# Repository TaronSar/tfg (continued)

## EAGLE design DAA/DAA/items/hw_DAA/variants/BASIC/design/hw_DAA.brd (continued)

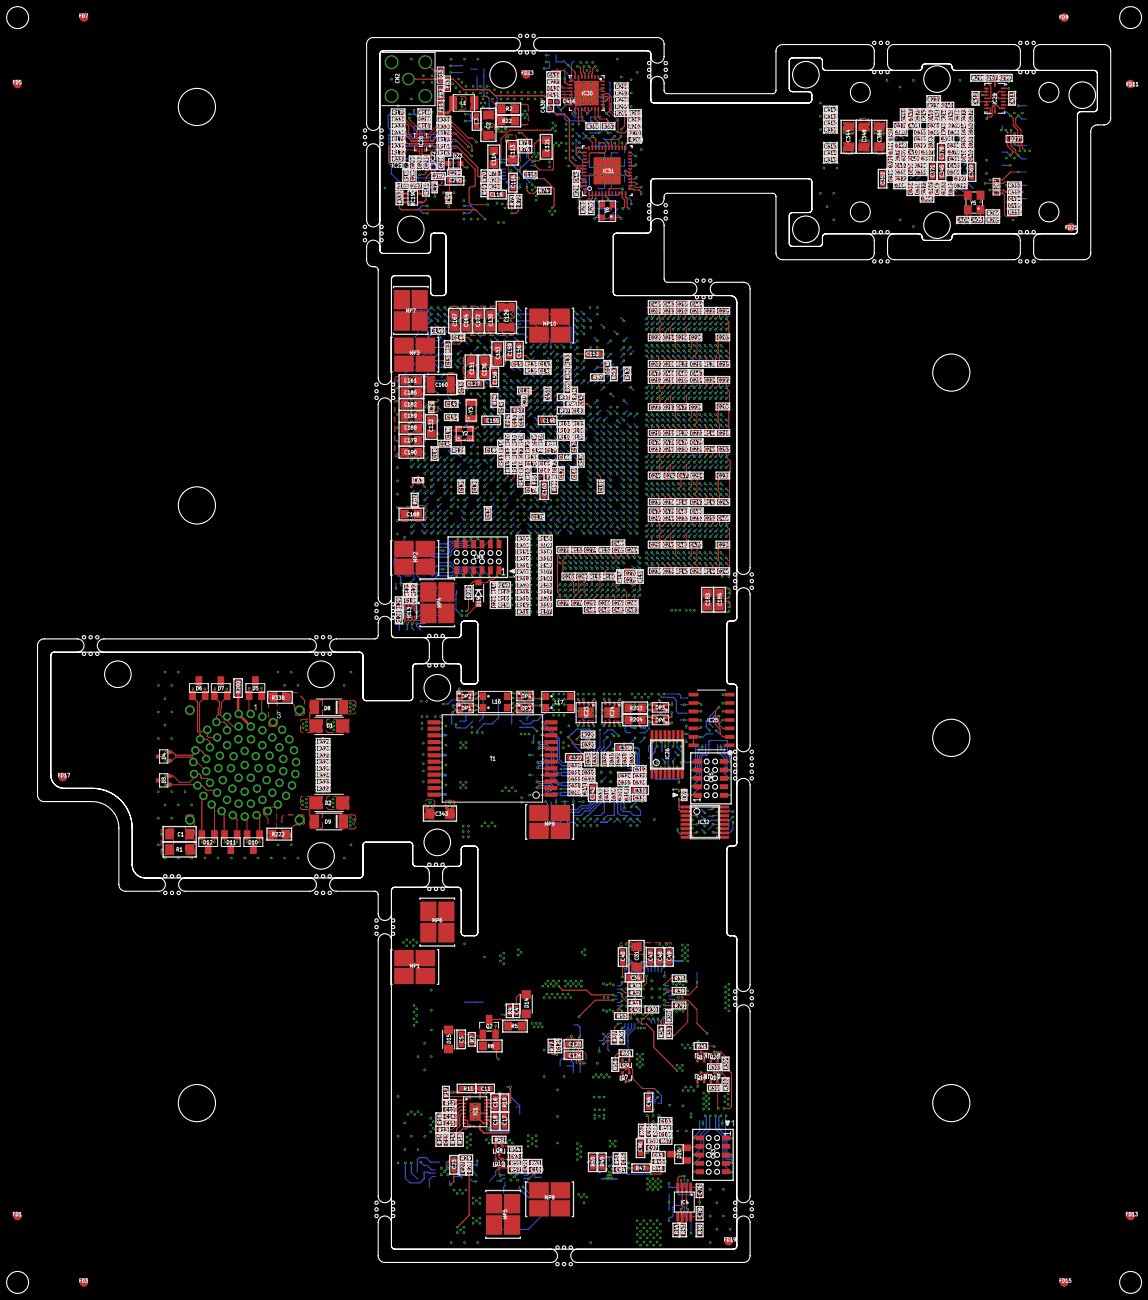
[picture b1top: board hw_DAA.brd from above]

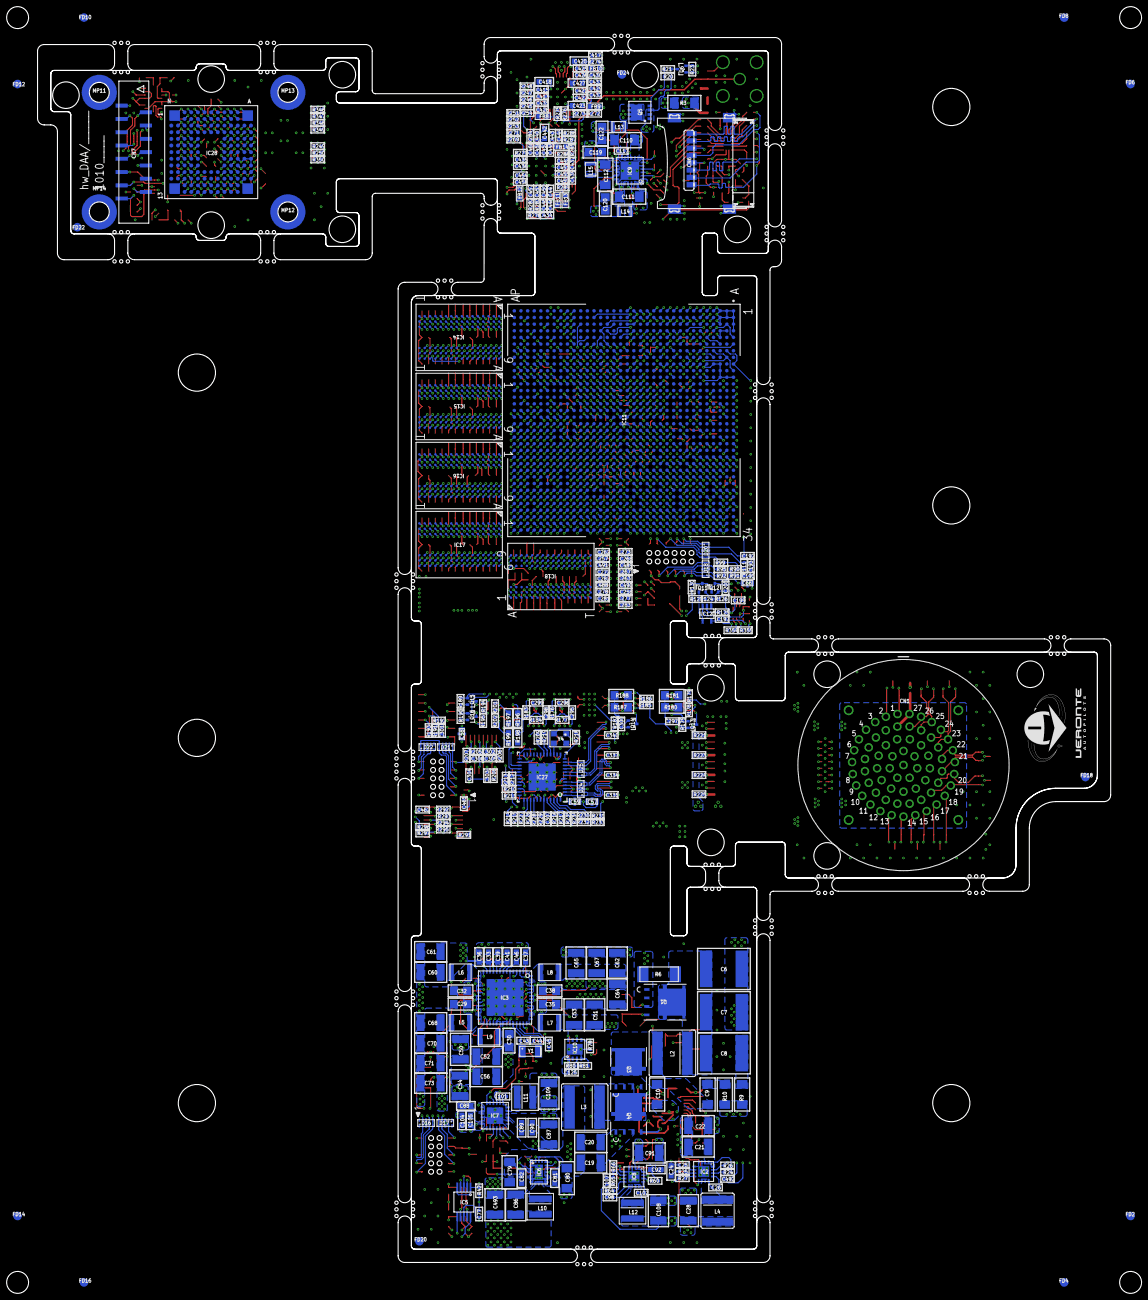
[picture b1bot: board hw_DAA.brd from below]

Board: 16 copper layers, 161.6 x 184.5 mm, 1022 parts (366 on the bottom side), 632 nets.

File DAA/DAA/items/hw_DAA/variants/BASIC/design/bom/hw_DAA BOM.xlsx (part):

Version | 101010
Schematics Name | hw_DAA.sch
Designer Name | Embention Sistemas Inteligentes S.A.
Date | 45559.0
QUANTITY | VALUE | DEVICE | PARTS | P/Ns
121 | 100nF,10%,0402,50V | C_0402 | C101, C102, C117, C137, C173, C192, C193, C196, C197, C199, C221, C224, C225, C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 | GCM155R71H104KE02D | GCM155L8EH104KE07D
7 | 100nF,10%,0603,100V | C_0603 | C11, C16, C3, C81, C82, C90, C92 | HMJ107BB7104KAHT | MCJCH168BB7104KTPA01
1 | 100pF,5%,0402,50V | C_0402 | C198 | GCM1555C1H101JA16D
18 | 100uF,20%,0805,4V | C_0805 | C130, C131, C132, C133, C136, C161, C164, C167, C168, C172, C179, C182, C183, C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 | GRM21BC80G107ME15L | GRM21BC80G107ME15K | CL21X107MRYN3WE
3 | 100uF,20%,1210,6.3V | C_1210 | C108, C109, C86 | GRT32ER60J107ME13L
19 | 10nF,10%,0402,50V | C_0402 | C284, C307, C325, C328, C335, C341, C413, C421, C425, C428, C429, C430, C447, C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 | CGA2B3X8R1H103K050BB
1 | 10pF,1%,0402,50V | C_0402 | C85 | GCQ1555C1H100FB01D
11 | 10uF,10%,0805,16V | C_0805 | C113, C114, C119, C120, C121, C122, C29, C30, C32, C35, C38 | EMK212BBJ106KGHT | CGA4J1X5R1C106K125AC
4 | 10uF,10%,1206,35V | C_1206 | C110, C111, C112, C2 | CGA5L1X7R1V106K160AC | CGA5L1X7R1H106K160AC
3 | 10uF,10%,2220,100V | C_2220K | C6, C7, C8 | CGA9N3X7S2A106K230KB
25 | 10uF,20%,0402,4V | C_0402 | C128, C141, C142, C143, C145, C146, C147, C148, C151, C153, C154, C157, C162, C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 | GRT155D70G106ME13J | GRT155D70G106ME13D | KAM05CT70G106KH
19 | 10uF,20%,0603,10V | C_0603 | C104, C105, C293, C327, C332, C338, C342, C345, C352, C369, C371, C378, C418, C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 | GRT188C81A106ME13D
10 | 10uF,20%,0603,4V,3L | NFM18HC106D0G3L | C55, C57, C58, C59, C63, C66, C69, C72, C74, C75 | NFM18HC106D0G3L
1 | 120pF,5%,0402,50V | C_0402 | C25 | GCM1555C1H121JA16D
2 | 12pF,5%,0402,50V | C_0402 | C43, C44 | GCM1555C1H120JA16J
2 | 15nF,10%,0402,50V | C_0402 | C419, C441 | GCM155R71H153KA55D
2 | 1nF,10%,1206,2KV | C_1206 | C1, C343 | C1206C102KGRACAUTO
64 | 1uF,10%,0402,25V | C_0402 | C115, C209, C212, C215, C218, C219, C220, C222, C223, C237, C240, C243, C246, C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 | GRT155R61E105KE01D
2 | 1uF,10%,0603,16V | C_0603 | C34, C94 | C0603C105K4RACAUTO
12 | 2.2uF,10%,0402,16V | C_0402 | C213, C214, C216, C217, C241, C242, C244, C245, C269, C270, C417, C440 | GRT155C81C225KE13D
16 | 2.2uF,10%,0603,16V | C_0603 | C116, C118, C123, C126, C18, C33, C36, C37, C39, C40, C41, C46, C47, C48, C49, 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 | CGA3E1X7S1C225K080AC
3 | 2.7nF,5%,0603,50V | C_0603 | C23, C24, C96 | C0603X272J5GAC7867
2 | 220nF,10%,0402,35V | C_0402 | C103, C408 | CGA2B1X7R1V224K050BC
1 | 22nF,10%,0402,50V | C_0402 | C414 | C0402C223K5RECAUTO
4 | 22pF,0.25pF,0402,50V | C_0402 | C100, C194, C195, C97 | 04025A220C4T2A
4 | 22uF,10%,1206,16V | C_1206 | C31, C344, C348, C386 | GRT31CC81C226KE01L
2 | 3.3nF,10%,0402,50V | C_0402 | C95, C98 | GCM155R71H332KA37J
1 | 330pF,10%,0402,50V | C_0402 | C106 | GRT155R71H331KE01D
2 | 330uF,20%,1210,2.5V | C_1210 | C129, C160 | GRM32EC80E337ME05L
1 | 33nF,10%,0402,50V | C_0402 | C438 | CGA2B3X7R1H333K050BB | GCM155R71H333KE02D
1 | 33pF,5%,0402,50V | C_0402 | C191 | GCM1555C1H330JA16D
1 | 390pF,10%,0402,50V | C_0402 | C13 | GCM155R71H391KA37D
3 | 4.7nF,20%,0402,100V | C_0402 | C297, C300, C84 | GCM155R72A472MA37D | GCM155R72A472KA37D | CL05B472KC5VPNC
50 | 4.7uF,20%,0402,10V | C_0402 | C135, C138, C139, C144, C149, C150, C201, C202, C203, C204, C205, C206, C207, C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 | GRT155R61A475ME13D
4 | 4.7uF,20%,1206,100V | C_1206 | C10, C79, C80, C9 | GRM31CC72A475ME11L
13 | 470nF,10%,0402,16V | C_0402 | C134, C171, C255, C42, C463, C466, C469, C474, C476, C479, C481, C483, C485 | CGA2B1X7S1C474K050BC
21 | 47uF,10%,1210,10V | C_1210 | C21, C22, C28, C50, C51, C52, C53, C54, C56, C60, C61, C62, C64, C65, C67, C68,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 | GCM32EC71A476KE02K
8 | 47uF,20%,0603,4V | C_0603 | C127, C140, C152, C155, C156, C158, C159, C163 | AMK107BC6476MA-RE | MSASA168BC6476MRCA01
1 | 56nF,10%,0402,16V | C_0402 | C12 | GCM155R71C563KA55J
1 | 6.8pF,5%,0603,100V | C_0603 | C17 | 06031A6R8J4T4A | CGA3E2NP02A6R8D080AA
2 | 6.8uF,20%,1210,50V | C_1210 | C19, C20 | CGA6P3X7S1H685M250AB
10 | 68nF,10%,0402,50V | C_0402 | C256, C464, C467, C471, C475, C477, C480, C482, C484, C486 | CGA2B3X7R1H683K050BB
2 | 8.2nF,10%,0402,16V | C_0402 | C14, C99 | C0402C822K4RACAUTO
2 | 820pF,10%,0402,50V | C_0402 | C15, C405 | GCG155R71H821KA01D
1 | 132203-18 | 132203-18 | CN2 | 132203-18
1 | 47219-2001 | SD-LATCH | CN6 | 47219-2001
2 | CLP-105-02-F-D-BE | CLP-105-02-F-D-BE | CN3, CN5 | CLP-105-02-F-D-BE
1 | CLP-106-02-F-D-BE | CLP-106-02-F-D-BE | CN4 | CLP-106-02-F-D-BE
1 | AQ4020-01FTG | AQ4020-01FTG | D23 | AQ4020-01FTG
2 | BZD27C10P-HE3-08 | BZD27C10P-HE3-08 | D14, D15 | BZD27C10P-HE3-08
1 | BZT52C3V3-7-F | BZT52C3V3-7-F | D19 | BZT52C3V3-7-F
4 | GSOT05C-HE3-08 | GSOT05C-HE3-08 | D10, D11, D12, D26 | GSOT05C-HE3-08
3 | HSP051-4M10 | HSP051-4M10CN | D24, D25, D27 | HSP051-4M10
1 | PESD15VL2BT-QR | SP712-02HTG | D5 | PESD15VL2BT-QR
2 | PESD2CANFD27V-UX | PESD2CANFD27V-UX | D3, D4 | PESD2CANFD27V-UX
7 | RCLAMP3324PQTCT | RCLAMP3324PQTCT | D16, D17, D18, D20, D21, D22, D28 | RCLAMP3324PQTCT
2 | SMA6J64CA | SZ1SMA36CAT3G | D1, D2 | SMA6J64CA
2 | SP712-02HTG | SP712-02HTG | D6, D7 | SP712-02HTG
2 | STPS5H100AFY | PMEG10030ELPX | D8, D9 | STPS5H100AFY
4 | BLM15PX121SH1D | BLM15PX121SH1D | FB4, FB5, FB6, FB7 | BLM15PX121SH1D
7 | BLM18AG102BH1D | BLM18HE152SZ1D | FB10, FB11, FB12, FB13, FB14, FB8, FB9 | BLM18AG102BH1D
3 | BLM18HE152SZ1D | BLM18HE152SZ1D | FB1, FB2, FB3 | BLM18HE152SZ1D
1 | BMI088 | BMI088 | IC29 | BMI088
1 | DP83867ERGZT | DP83867ERGZ | IC27 | DP83867ERGZT
1 | DS90UB954TRGZTQ1 | DS90UB954-Q1 | IC31 | DS90UB954TRGZTQ1
2 | ECS-2520MVQ-250-CN-TR | ECS-2520MVQ-250-CN-TR | Y4, Y6 | ECS-2520MVQ-250-CN-TR
1 | IMX296LQR-C | IMX296NSMD | IC28 | IMX296LQR-C
1 | LM5146QRGYRQ1 | LM5146-Q1 | IC1 | LM5146QRGYRQ1
5 | MT40A1G16TD-062E AAT_F | MT40A1G16TD-062ENSMD | IC14, IC15, IC16, IC17, IC18 | MT40A1G16TD-062E AAT:F
1 | NVT4858HK | NVT4858HK | IC20 | NVT4858HK
1 | SIT8008BI-11-33E-33.333333 | SIT8008BI-11-33E-33.333333 | Y2 | SiT8008BI-11-33E-33.333333E
1 | SN65C3221IPWRQ1 | SN65C3221-Q1 | IC26 | SN65C3221IPWRQ1
1 | SN65HVD33MDREP | SN65HVD33 | IC25 | SN65HVD33MDREP
1 | SN74LVC1G04QDCKRQ1 | SN74LVC1G04QDCKRQ1 | IC19 | SN74LVC1G04QDCKRQ1
1 | SN74LVC1G08QDCKRQ1 | SN74LVC1G08QDCKRQ1 | IC12 | SN74LVC1G08QDCKRQ1
1 | SiT8008BI-22-18E-37.125000G | SIT8008BI-22-18E-37.125000 | Y5 | SiT8008BI-22-18E-37.125000G
1 | TCA9517DGKRQ1 | TCA9517-Q1 | IC4 | TCA9517DGKRQ1
2 | TCAN1462VDRBRQ1 | TCAN1462V-Q1VSON-8 | IC23, IC24 | TCAN1462VDRBRQ1
4 | TLP3431(TP,F | TLP3431 | OP1, OP2, OP3, OP4 | TLP3431(TP,F
2 | TLP3475(TP,F | TLP3431 | OP5, OP6 | TLP3475(TP,F
1 | TMP451HQDQFRQ1 | TMP451-Q1 | IC13 | TMP451HQDQFRQ1
2 | TPS22910AYZVR | TPS2291XX | IC21, IC22 | TPS22910AYZVR
1 | TPS54116QRTWTQ1 | TPS54116-Q1 | IC7 | TPS54116QRTWTQ1
2 | TPS57112CQRTERQ1 | TPS57112C-Q1 | IC2, IC8 | TPS57112CQRTERQ1
1 | TPS62873QWRXSRQ1 | TPS62873-Q1 | IC6 | TPS62873QWRXSRQ1
1 | TPS65033000RGERQ1 | TPS650330-Q1 | IC9 | TPS65033000RGERQ1
1 | TPS65930400RWERQ1 | TPS6593-Q1 | IC3 | TPS65930400RWERQ1
1 | TPS74525PQWDRBRQ1 | TPS745-Q1 | IC10 | TPS74525PQWDRBRQ1
1 | TS5A23157TDGSRQ1 | TS5A23157-Q1 | IC5 | TS5A23157TDGSRQ1
1 | TXB0106IPWRQ1 | TXB0106-Q1 | IC32 | TXB0106IPWRQ1
1 | XCZU15EG-2FFVB1156I | XCZU15EG-FFVB1156 | IC11 | XCZU15EG-2FFVB1156I
1 | 1.5uH,20%,2.3A | L201610 | L13 | TFM201610ALMA1R5MTAA
1 | 1.5uH,20%,9.1A | XAL4020 | L12 | XFL4020-152MEC
1 | 100nH,20%,19.9A | XAL4020 | L10 | XEL4020-101MEC
1 | 10uH,10%,450mA | NLCV32T-100K-EFRD | L1 | NLCV32T-100K-EFRD
2 | 1812CAN-113NRC | 1812CAN | L16, L17 | 1812CAN-113NRC
2 | 1uH,20%,3.1A | L201610 | L14, L15 | TFM201610ALMA1R0MTAA
1 | 2.2uH,20%,9.7A | XAL50XX | L4 | XAL5030-222MEC
3 | 220nH,20%,7A | TFM322512ALMA | L5, L8, L9 | TFM322512ALMAR22MTAA
2 | 4.7uH,20%,9A | XAL7030472 | L2, L3 | XAL7030-472MEC
2 | 470nH,20%,5.3A | TFM322512ALMA | L6, L7 | TFM322512ALMAR47MTAA
1 | 600nH,20%,11.7A | XAL4020 | L11 | XAL4020-601MEC
1 | HX5008NL | HX5008NL | T1 | HX5008NL
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
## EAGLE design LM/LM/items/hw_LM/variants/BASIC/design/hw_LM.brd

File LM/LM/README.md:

# LM
Veronte Autopilot LM (Loitering Munition)

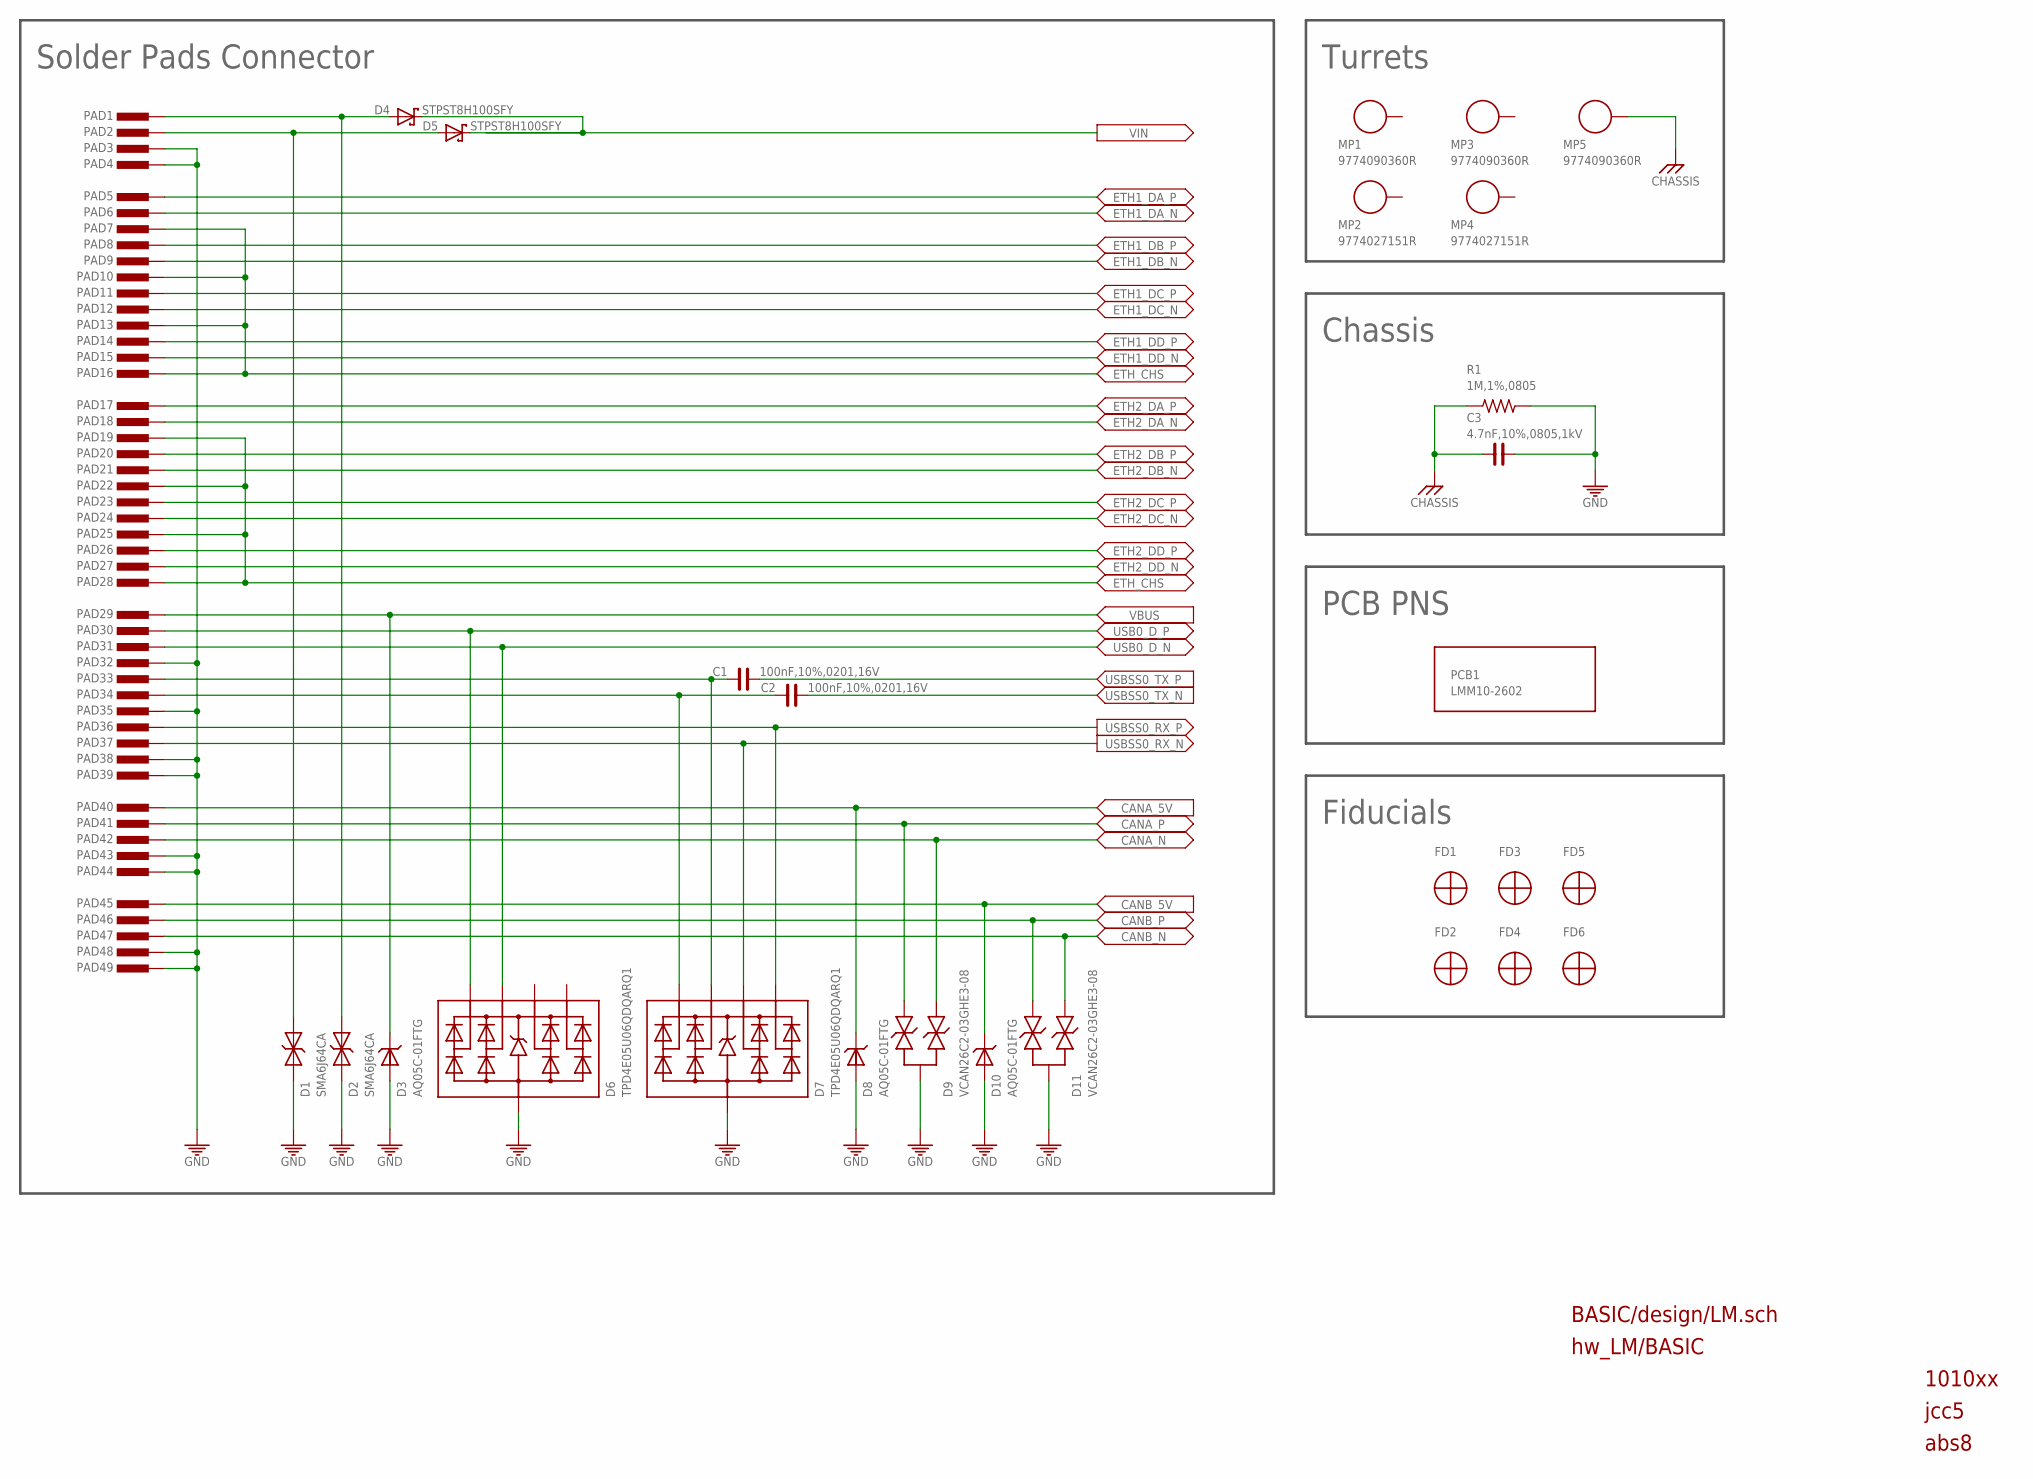
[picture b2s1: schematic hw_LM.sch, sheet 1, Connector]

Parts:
C1, C2: 100nF,10%,0201,16V; C0201
C3: 4.7nF,10%,0805,1kV; C0805
D1, D2: SMA6J64CA; SMA_BI
D3, D8, D10: AQ05C-01FTG; SOD-323
D4, D5: STPST8H100SFY; TO-277A-3
D6, D7: TPD4E05U06QDQARQ1; DQA(R-PUSON-N10)
D9, D11: VCAN26C2-03GHE3-08; SOT323-3
FD1, FD2, FD3, FD4, FD5, FD6: NOPOP; FIDU
MP1, MP3, MP5: 9774090360R; 9774050360R
MP2, MP4: 9774027151R; WA-SMSI_9774027151
PAD1, PAD2, PAD3, PAD4: NOPOP; PAD_SMD_5X1.25
PAD5, PAD6, PAD7, PAD8, PAD9, PAD10, PAD11, PAD12, PAD13, PAD14, PAD15, PAD16, PAD17, PAD18, PAD19, PAD20, PAD21, PAD22, PAD23, PAD24, PAD25, PAD26, PAD27, PAD28, PAD30, PAD31, PAD32, PAD33, PAD34, PAD35, PAD36, PAD37, PAD38, PAD40, PAD41, PAD42, PAD43, PAD44, PAD45, PAD46, PAD47, PAD48, PAD49: NOPOP; PAD_SMD_5X0.8
PAD29, PAD39: NOPOP; PAD_SMD_5X1
PCB1: LMM10-2602; VOID
R1: 1M,1%,0805; R0805

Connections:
BAT1: D2.2, D4.A1 (A), D4.A2 (A), PAD1.1
BAT2: D1.2, D5.A1 (A), D5.A2 (A), PAD2.1
CANA_5V: D8.K, PAD40.1; also elsewhere on the board
CANA_N: D9.1, PAD42.1; also elsewhere on the board
CANA_P: D9.2, PAD41.1; also elsewhere on the board
CANB_5V: D10.K, PAD45.1; also elsewhere on the board
CANB_N: D11.1, PAD47.1; also elsewhere on the board
CANB_P: D11.2, PAD46.1; also elsewhere on the board
CHASSIS: C3.2, MP5.1, R1.2
ETH1_DA_N: PAD6.1; also elsewhere on the board
ETH1_DA_P: PAD5.1; also elsewhere on the board
ETH1_DB_N: PAD9.1; also elsewhere on the board
ETH1_DB_P: PAD8.1; also elsewhere on the board
ETH1_DC_N: PAD12.1; also elsewhere on the board
ETH1_DC_P: PAD11.1; also elsewhere on the board
ETH1_DD_N: PAD15.1; also elsewhere on the board
ETH1_DD_P: PAD14.1; also elsewhere on the board
ETH2_DA_N: PAD18.1; also elsewhere on the board
ETH2_DA_P: PAD17.1; also elsewhere on the board
ETH2_DB_N: PAD21.1; also elsewhere on the board
ETH2_DB_P: PAD20.1; also elsewhere on the board
ETH2_DC_N: PAD24.1; also elsewhere on the board
ETH2_DC_P: PAD23.1; also elsewhere on the board
ETH2_DD_N: PAD27.1; also elsewhere on the board
ETH2_DD_P: PAD26.1; also elsewhere on the board
ETH_CHS: PAD7.1, PAD10.1, PAD13.1, PAD16.1, PAD19.1, PAD22.1, PAD25.1, PAD28.1; also elsewhere on the board
GND: C3.1, D1.1, D2.1, D3.A, D6.3 (CA), D6.8 (CA), D7.3 (CA), D7.8 (CA), D8.A, D9.3, D10.A, D11.3, PAD3.1, PAD4.1, PAD32.1, PAD35.1, PAD38.1, PAD39.1, PAD43.1, PAD44.1, PAD48.1, PAD49.1, R1.1; also elsewhere on the board
USB0_D_N: D6.2 (K2), D6.9 (K2), PAD31.1; also elsewhere on the board
USB0_D_P: D6.1 (K1), D6.10 (K1), PAD30.1; also elsewhere on the board
USBSS0_RX_N: D7.2 (K2), D7.9 (K2), PAD37.1; also elsewhere on the board
USBSS0_RX_P: D7.1 (K1), D7.10 (K1), PAD36.1; also elsewhere on the board
USBSS0_TX_N: C2.1; also elsewhere on the board
USBSS0_TX_P: C1.1; also elsewhere on the board
USB_TX_N: C2.2, D7.5 (K4), D7.6 (K4), PAD34.1
USB_TX_P: C1.2, D7.4 (K3), D7.7 (K3), PAD33.1
VBUS: D3.K, PAD29.1; also elsewhere on the board
VIN: D4.K (C), D5.K (C); also elsewhere on the board

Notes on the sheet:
BASIC/design/LM.sch
hw_LM/BASIC
1010xx
jcc5
abs8
Solder Pads Connector
PCB PNS
Fiducials
Chassis
Turrets

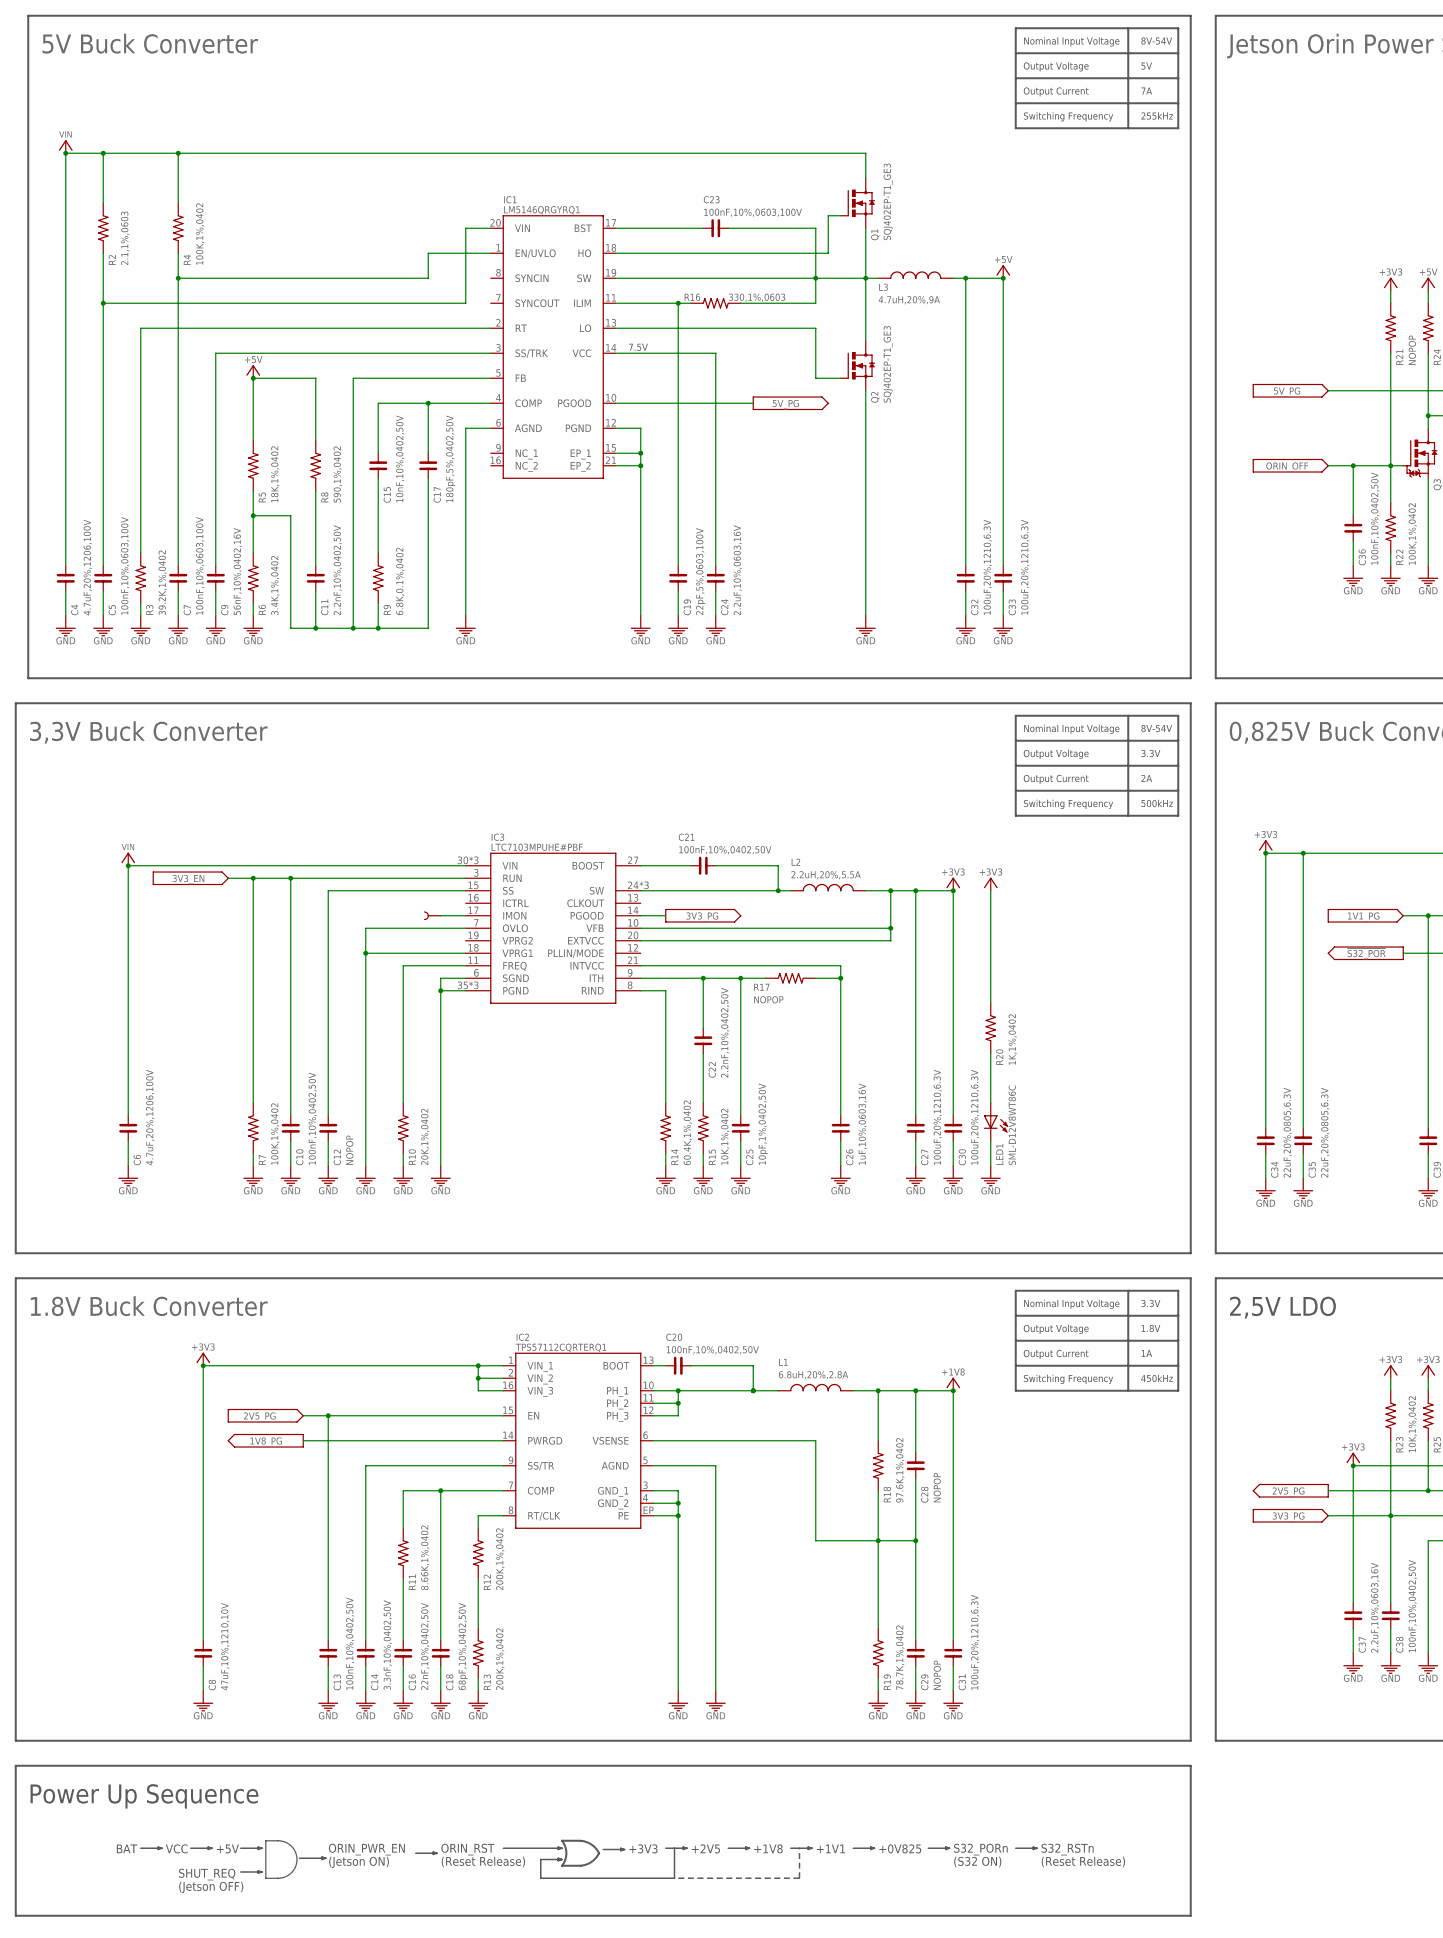
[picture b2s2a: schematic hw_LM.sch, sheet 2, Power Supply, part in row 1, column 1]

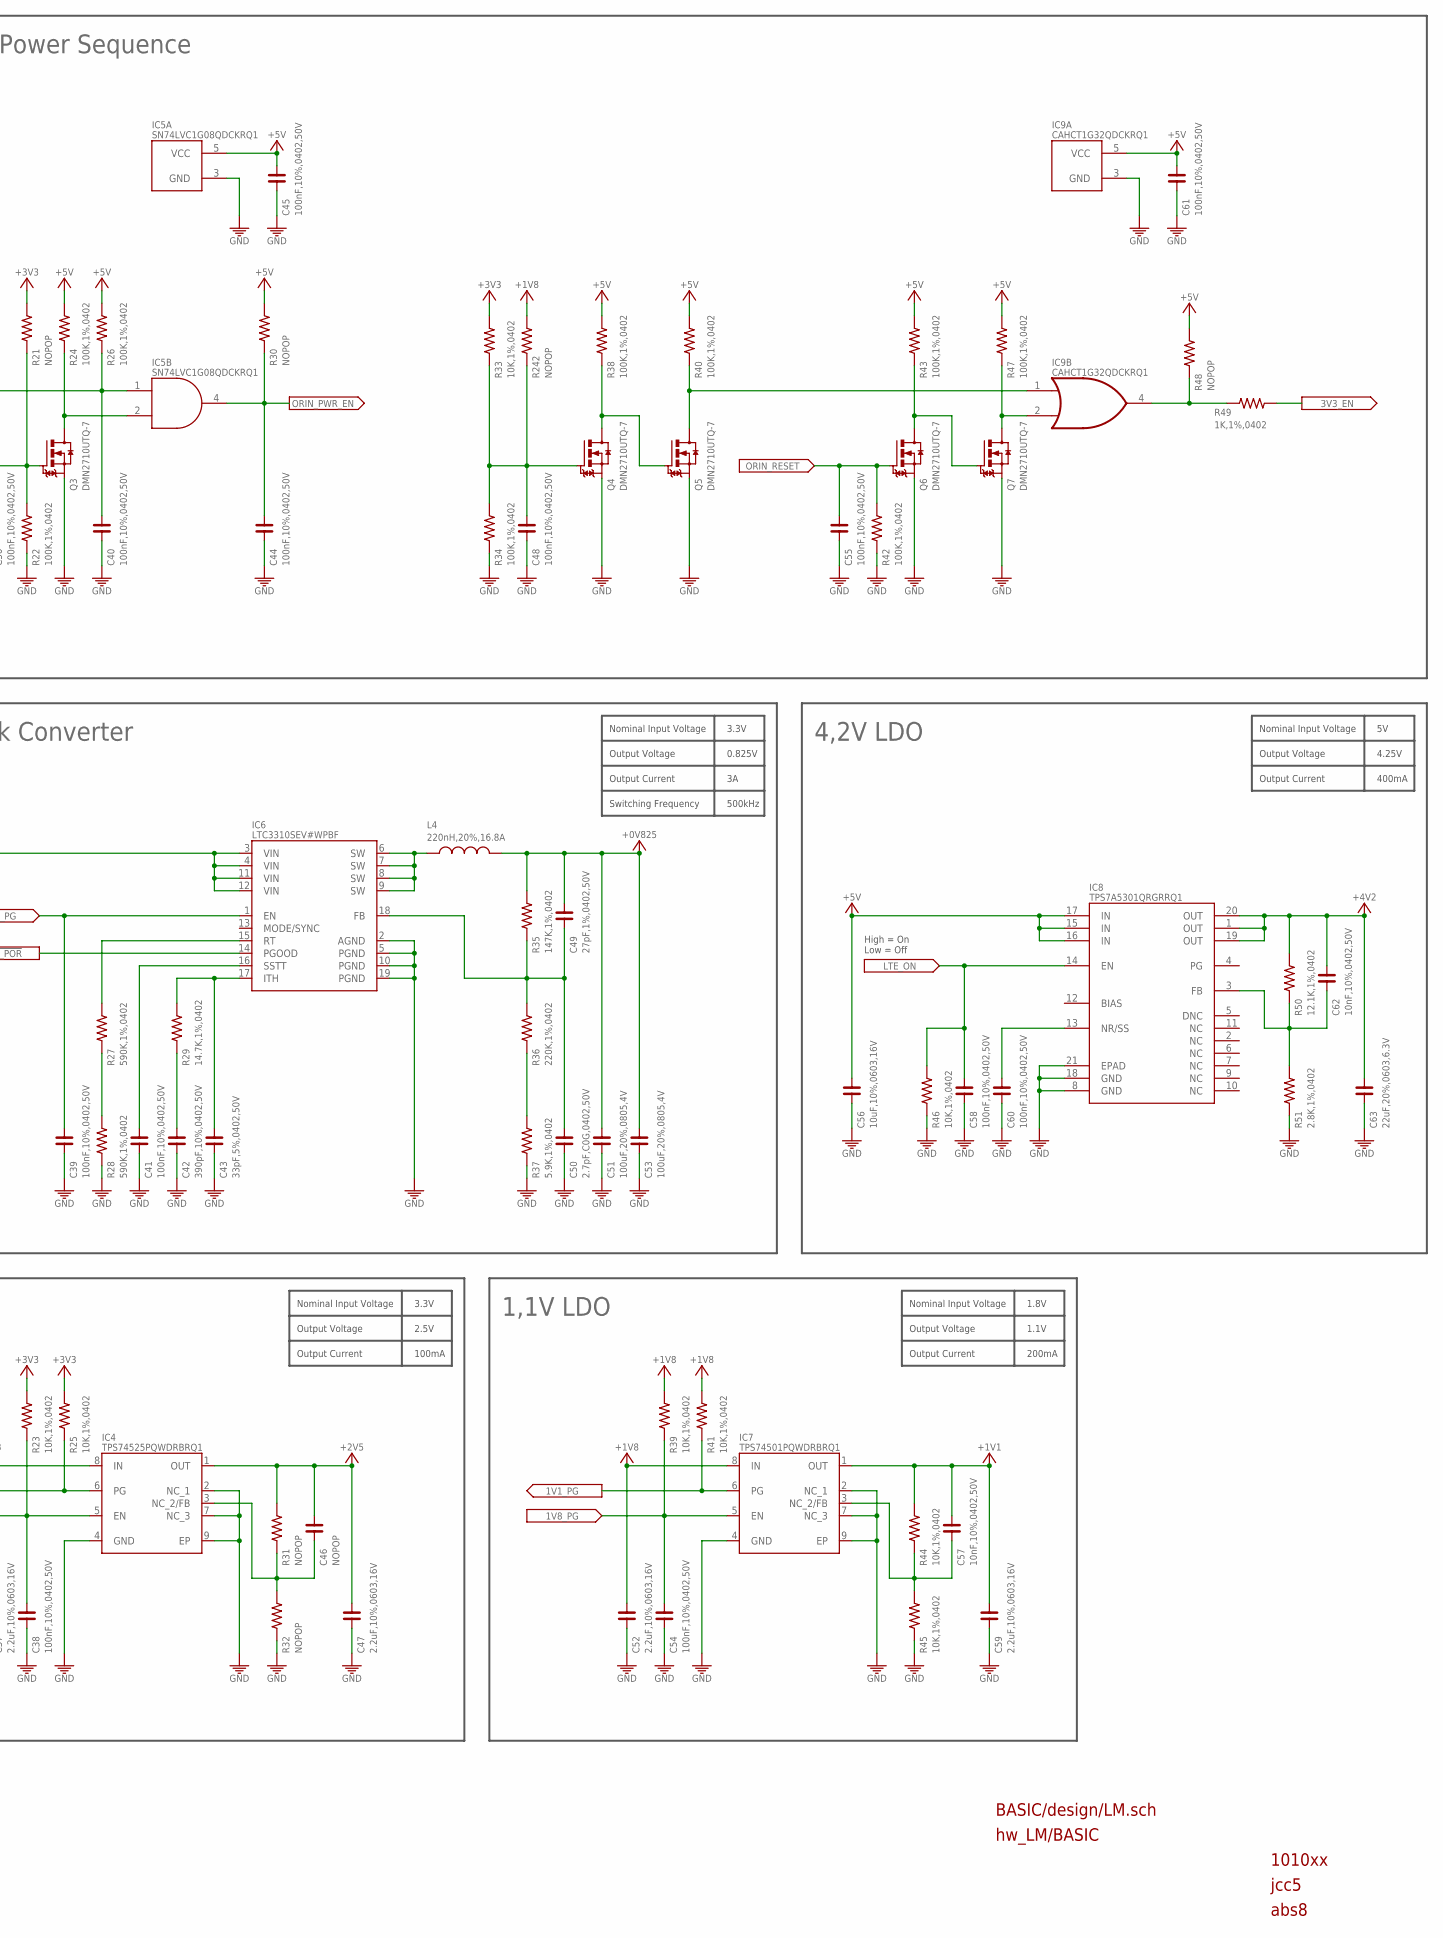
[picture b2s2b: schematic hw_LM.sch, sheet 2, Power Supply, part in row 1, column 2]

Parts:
C4, C6: 4.7uF,20%,1206,100V; C1206
C5, C7, C23: 100nF,10%,0603,100V; C0603
C8: 47uF,10%,1210,10V; C1210
C9: 56nF,10%,0402,16V; C0402
C10, C13, C20, C21, C36, C38, C39, C40, C41, C44, C45, C48, C54, C55, C58, C60, C61: 100nF,10%,0402,50V; C0402
C11, C22: 2.2nF,10%,0402,50V; C0402
C12, C28, C29, C46: NOPOP; C0402
C14: 3.3nF,10%,0402,50V; C0402
C15, C57, C62: 10nF,10%,0402,50V; C0402
C16: 22nF,10%,0402,50V; C0402
C17: 180pF,5%,0402,50V; C0402
C18: 68pF,10%,0402,50V; C0402
C19: 22pF,5%,0603,100V; C0603
C24, C37, C47, C52, C59: 2.2uF,10%,0603,16V; C0603
C25: 10pF,1%,0402,50V; C0402
C26: 1uF,10%,0603,16V; C0402
C27, C30, C31, C32, C33: 100uF,20%,1210,6.3V; C1210
C34, C35: 22uF,20%,0805,6.3V; C0805
C42: 390pF,10%,0402,50V; C0402
C43: 33pF,5%,0402,50V; C0402
C49: 27pF,1%,0402,50V; C0402
C50: 2.7pF,C0G,0402,50V; C0402
C51, C53: 100uF,20%,0805,4V; C0805
C56: 10uF,10%,0603,16V; C0603
C63: 22uF,20%,0603,6.3V; C0603
IC1: LM5146QRGYRQ1; VQFN-20
IC2: TPS57112CQRTERQ1; WQFN-16
IC3: LTC7103MPUHE#PBF; UHE36(26)
IC4: TPS74525PQWDRBRQ1; VSON-8
IC5: SN74LVC1G08QDCKRQ1; DCK5
IC6: LTC3310SEV#WPBF; LQFN-18
IC7: TPS74501PQWDRBRQ1; VSON-8
IC8: TPS7A5301QRGRRQ1; VQFN-20(TEXAS)
IC9: CAHCT1G32QDCKRQ1; DCK5
L1: 6.8uH,20%,2.8A; IHLP2020CZER220M11
L2: 2.2uH,20%,5.5A; XAL4020
L3: 4.7uH,20%,9A; XAL7030-472
L4: 220nH,20%,16.8A; XAL4020
LED1: SML-D12V8WT86C; LED-0603
Q1, Q2: SQJ402EP-T1_GE3; SO-8L
Q3, Q4, Q5, Q6, Q7: DMN2710UTQ-7; SOT-523
R2: 2.1,1%,0603; R0603
R3: 39.2K,1%,0402; R0402
R4, R7, R22, R24, R26, R34, R38, R40, R42, R43, R47: 100K,1%,0402; R0402
R5: 18K,1%,0402; R0402
R6: 3.4K,1%,0402; R0402
R8: 590,1%,0402; R0402
R9: 6.8K,0.1%,0402; R0402
R10: 20K,1%,0402; R0402
R11: 8.66K,1%,0402; R0402
R12, R13: 200K,1%,0402; R0402
R14: 60.4K,1%,0402; R0402
R15, R23, R25, R33, R39, R41, R44, R45, R46: 10K,1%,0402; R0402
R16: 330,1%,0603; R0603
R17, R21, R30, R31, R32, R48, R242: NOPOP; R0402
R18: 97.6K,1%,0402; R0402
R19: 78.7K,1%,0402; R0402
R20, R49: 1K,1%,0402; R0402
R27, R28: 590K,1%,0402; R0402
R29: 14.7K,1%,0402; R0402
R35: 147K,1%,0402; R0402
R36: 220K,1%,0402; R0402
R37: 5.9K,1%,0402; R0402
R50: 12.1K,1%,0402; R0402
R51: 2.8K,1%,0402; R0402
TP1: NOPOP; PAD.02X.02

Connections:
0V825_FB: C49.1, C50.2, IC6.18 (FB), R35.1, R36.2
0V825_ITH: C43.2, IC6.17 (ITH), R29.2
0V825_RT: IC6.15 (RT), R27.2
0V825_SSTT: C41.2, IC6.16 (SSTT)
1V1_FB: C57.1, IC7.3 (NC_2/FB), R44.1, R45.2
1V1_PG: C39.2, IC6.1 (EN), IC7.6 (PG), R41.1
1V8_BOOT: C20.2, IC2.13 (BOOT)
1V8_COMP: C18.1, IC2.7 (COMP), R11.2
1V8_PG: C54.2, IC2.14 (PWRGD), IC7.5 (EN), R39.1
1V8_PH: C20.1, IC2.10 (PH_1), IC2.11 (PH_2), IC2.12 (PH_3), L1.P$1
1V8_RT: IC2.8 (RT/CLK), R12.2
1V8_SS: C14.1, IC2.9 (SS/TR)
1V8_VSENSE: C28.2, C29.1, IC2.6 (VSENSE), R18.1, R19.2
2V5_FB: C46.2, IC4.3 (NC_2/FB), R31.1, R32.2
2V5_PG: C13.2, IC2.15 (EN), IC4.6 (PG), R25.1
3V3_BST: C21.1, IC3.27 (BOOST)
3V3_EN: C10.2, IC3.3 (RUN), R7.1, R49.1
3V3_FREQ: IC3.11 (FREQ), R10.2
3V3_IMON: IC3.17 (IMON), TP1.P$1
3V3_INTVCC: C26.2, IC3.21 (INTVCC), R17.2
3V3_ITH: C22.2, C25.2, IC3.9 (ITH), R17.1
3V3_PG: C38.2, IC3.14 (PGOOD), IC4.5 (EN), R23.1
3V3_RIND: IC3.8 (RIND), R14.2
3V3_SS: C12.2, IC3.15 (SS)
3V3_SW: C21.2, IC3.24 (SW), IC3.25 (SW), IC3.26 (SW), L2.1
4V2_FB: C62.1, IC8.3 (FB), R50.1, R51.2
4V2_SS: C60.2, IC8.13 (NR/SS)
5V_BST: C23.2, IC1.17 (BST)
5V_COMP: C15.1, C17.1, IC1.4 (COMP)
5V_EN: C7.1, IC1.1 (EN/UVLO), R4.1
5V_FB: C11.2, C17.2, IC1.5 (FB), R5.1, R6.2, R9.1
5V_HO: IC1.18 (HO), Q1.4 (G)
5V_ILIM: C19.1, IC1.11 (ILIM), R16.2
5V_LO: IC1.13 (LO), Q2.4 (G)
5V_PG: C40.2, IC1.10 (PGOOD), IC5.1 (A), R26.2
5V_RT: IC1.2 (RT), R3.2
5V_SS: C9.1, IC1.3 (SS/TRK)
5V_SW: C23.1, IC1.19 (SW), L3.1, Q1.1 (S), Q1.2 (S), Q1.3 (S), Q2.5 (D), Q2.EP1 (D), Q2.EP2 (D), R16.1
5V_VCC: C24.1, IC1.14 (VCC)
5V_VIN: C5.1, IC1.20 (VIN), R2.1
!S32_POR: IC6.14 (PGOOD); also elsewhere on the board
+0V825: C49.2, C51.2, C53.2, L4.2, R35.2; also elsewhere on the board
+1V1: C57.2, C59.1, IC7.1 (OUT), R44.2; also elsewhere on the board
+1V8: C28.1, C31.2, C52.1, IC7.8 (IN), L1.P$2, R18.2, R39.2, R41.2, R242.1; also elsewhere on the board
+2V5: C46.1, C47.1, IC4.1 (OUT), R31.2; also elsewhere on the board
+3V3: C8.1, C27.2, C30.2, C34.2, C35.2, C37.1, IC2.1 (VIN_1), IC2.2 (VIN_2), IC2.16 (VIN_3), IC3.10 (VFB), IC3.20 (EXTVCC), IC4.8 (IN), IC6.3 (VIN), IC6.4 (VIN), IC6.11 (VIN), IC6.12 (VIN), L2.2, R20.2, R21.1, R23.2, R25.2, R33.1; also elsewhere on the board
+4V2: C62.2, C63.2, IC8.1 (OUT), IC8.19 (OUT), IC8.20 (OUT), R50.2; also elsewhere on the board
+5V: C32.2, C33.2, C45.2, C56.2, C61.2, IC5.5 (VCC), IC8.15 (IN), IC8.16 (IN), IC8.17 (IN), IC9.5 (VCC), L3.2, R5.2, R8.2, R24.1, R26.1, R30.1, R38.1, R40.1, R43.1, R47.1, R48.2; also elsewhere on the board
GND: C4.2, C5.2, C6.2, C7.2, C8.2, C9.2, C10.1, C12.1, C13.1, C14.2, C16.2, C18.2, C19.2, C24.2, C25.1, C26.1, C27.1, C29.2, C30.1, C31.1, C32.1, C33.1, C34.1, C35.1, C36.1, C37.2, C38.1, C39.1, C40.1, C41.1, C42.1, C43.1, C44.1, C45.1, C47.2, C48.1, C50.1, C51.1, C52.2, C53.1, C54.1, C55.1, C56.1, C58.1, C59.2, C60.1, C61.1, C63.1, IC1.6 (AGND), IC1.12 (PGND), IC1.15 (EP_1), IC1.21 (EP_2), IC2.3 (GND_1), IC2.4 (GND_2), IC2.5 (AGND), IC2.EP (PE), IC3.6 (SGND), IC3.7 (OVLO), IC3.18 (VPRG1), IC3.35 (PGND), IC3.36 (PGND), IC3.37 (PGND), IC4.2 (NC_1), IC4.4 (GND), IC4.7 (NC_3), IC4.9 (EP), IC5.3 (GND), IC6.2 (AGND), IC6.5 (PGND), IC6.10 (PGND), IC6.19 (PGND), IC7.2 (NC_1), IC7.4 (GND), IC7.7 (NC_3), IC7.9 (EP), IC8.8 (GND), IC8.18 (GND), IC8.21 (EPAD), IC9.3 (GND), LED1.C, Q2.1 (S), Q2.2 (S), Q2.3 (S), Q3.2 (S), Q4.2 (S), Q5.2 (S), Q6.2 (S), Q7.2 (S), R3.1, R6.1, R7.2, R10.1, R13.1, R14.1, R15.1, R19.1, R22.2, R28.1, R32.1, R34.2, R37.1, R42.2, R45.1, R46.2, R51.1; also elsewhere on the board
LTE_ON: C58.2, IC8.14 (EN), R46.1; also elsewhere on the board
unnamed: C48.2, Q4.1 (G), R33.2, R34.1, R242.2
unnamed: IC9.1 (A), Q5.3 (D), R40.2
unnamed: R12.1, R13.2
unnamed: Q4.3 (D), Q5.1 (G), R38.2
unnamed: Q6.3 (D), Q7.1 (G), R43.2
unnamed: IC9.2 (B), Q7.3 (D), R47.2
unnamed: C15.2, R9.2
unnamed: C42.2, R29.1
unnamed: R36.1, R37.2
unnamed: C11.1, R8.1
unnamed: IC6.6 (SW), IC6.7 (SW), IC6.8 (SW), IC6.9 (SW), L4.1
unnamed: R27.1, R28.2
unnamed: IC9.4 (Y), R48.1, R49.2
unnamed: C22.1, R15.2
unnamed: C16.1, R11.1
unnamed: LED1.A, R20.1
ORIN_OFF: C36.2, Q3.1 (G), R21.2, R22.1; also elsewhere on the board
ORIN_OFF_N: IC5.2 (B), Q3.3 (D), R24.2
ORIN_PWR_EN: C44.2, IC5.4 (Y), R30.2; also elsewhere on the board
ORIN_RESET: C55.2, Q6.1 (G), R42.1; also elsewhere on the board
VIN: C4.1, C6.1, IC3.30 (VIN), IC3.31 (VIN), IC3.32 (VIN), Q1.5 (D), Q1.EP1 (D), Q1.EP2 (D), R2.2, R4.2; also elsewhere on the board

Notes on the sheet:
BASIC/design/LM.sch
hw_LM/BASIC
1010xx
jcc5
abs8
High = On Low = Off
5V Buck Converter
3,3V Buck Converter
0,825V Buck Converter
4,2V LDO
1,1V LDO
7.5V
2,5V LDO
Jetson Orin Power Sequence
Output Voltage
Output Current
4.25V
400mA
Nominal Input Voltage
1.1V
200mA
1.8V
2.5V
100mA
3.3V
8V-54V
0.825V
Switching Frequency
500kHz
450kHz
255kHz
1.8V Buck Converter
Power Up Sequence
BAT
VCC
+5V
ORIN_PWR_EN (Jetson ON)
ORIN_RST (Reset Release)
+3V3
+2V5
